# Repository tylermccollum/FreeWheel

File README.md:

BLDC motors represent an opportunity for massive improvements in hobby 
robotics work, but is largely limited by the cost. You can get a 
serviceable motor for less than $5, but the driver to use it starts at 
$40. The goal for this project is to create an open-source 100W BLDC 
servo controller design with a BOM cost under $10 and an accompanying 
library for control to standardize open-source FOC work.

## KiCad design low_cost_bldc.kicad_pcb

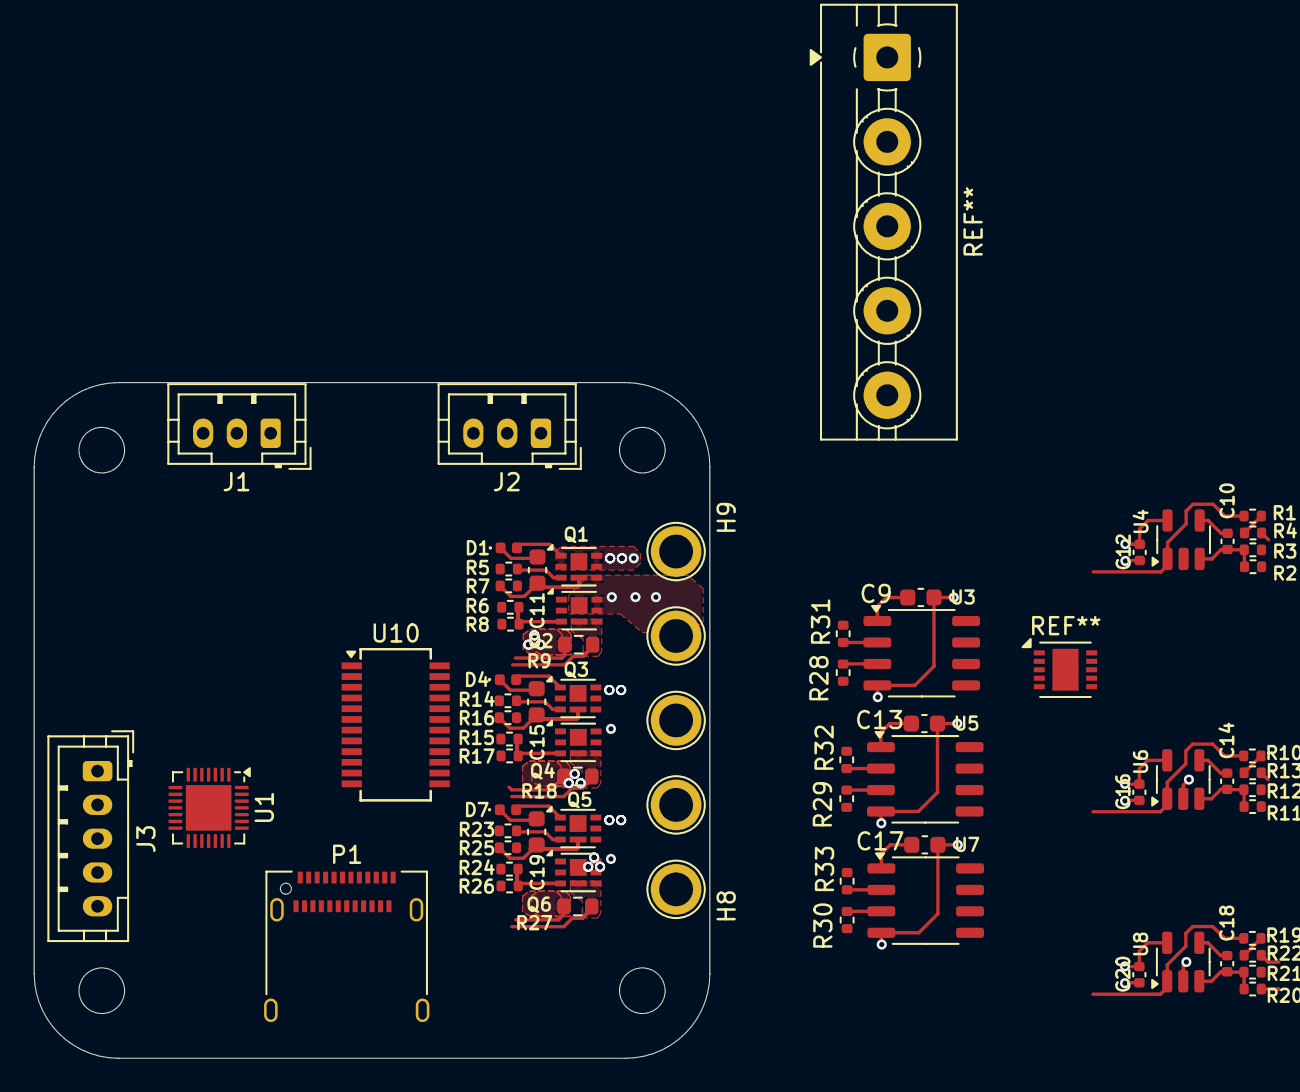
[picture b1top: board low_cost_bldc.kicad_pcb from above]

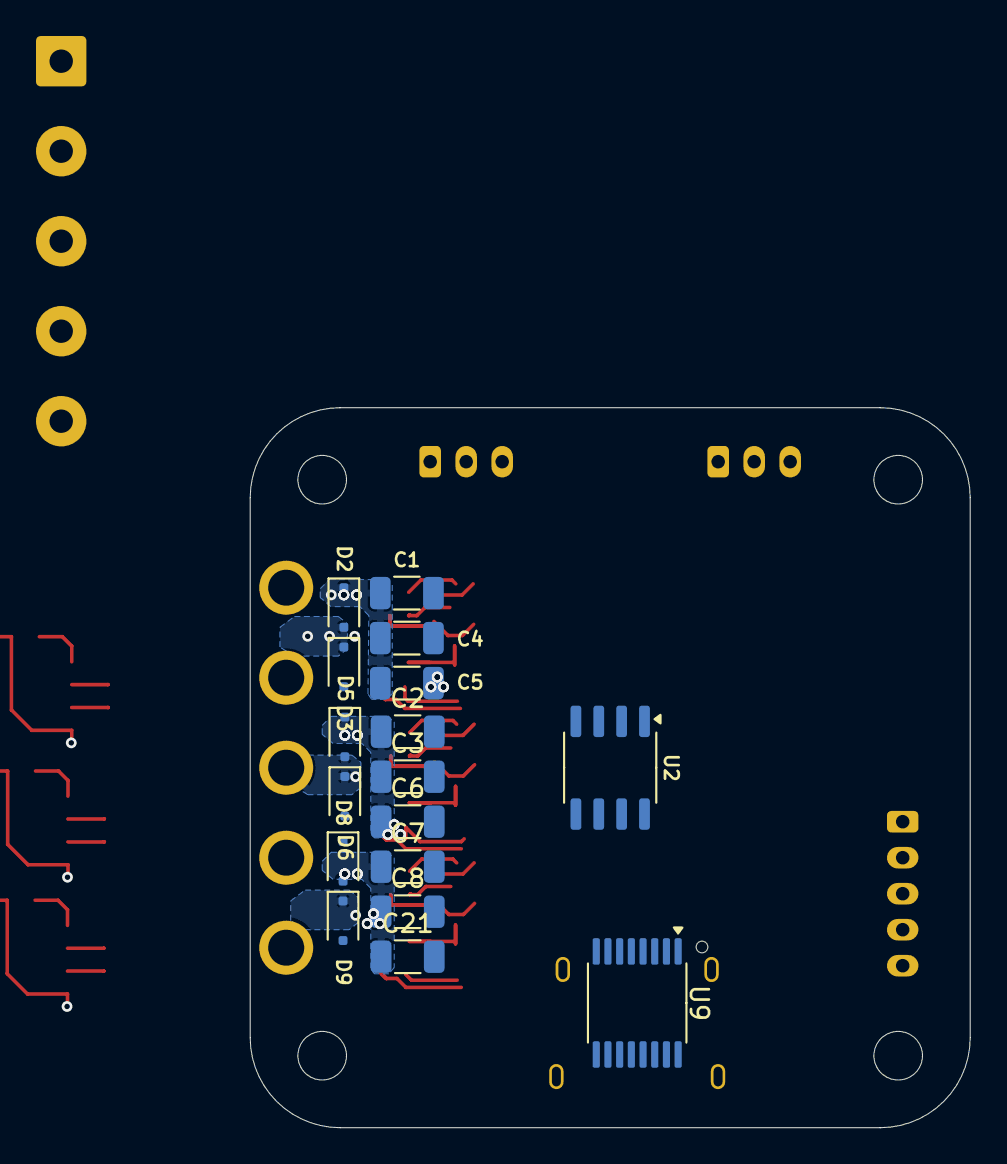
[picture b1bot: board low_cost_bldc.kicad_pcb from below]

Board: 4 copper layers, 40.0 x 40.0 mm, 92 parts (17 on the bottom side), 43 nets.

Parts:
C1, C2, C3, C4, C5, C6, C7, C8, C21: 10uF; C_1206_3216Metric
C9, C11, C13, C15, C17, C19: 1uF; C_0603_1608Metric
C10, C14, C18: C_Small; C_0402_1005Metric
C12, C16, C20: 0.1uF; C_0402_1005Metric
D1, D4, D7: D_Schottky_Filled; D_0402_1005Metric
D2, D3, D5, D6, D8, D9: D_Schottky_Filled; D_SOD-323F
H1, H2, H3, H4: MountingHole; MountingHole_2.7mm_M2.5
H5, H6, H7, H8, H9: MountingHole_Pad; TestPoint_Plated_Hole_D2.0mm
J1, J2: Conn_01x03; JST_PH_B3B-PH-K_1x03_P2.00mm_Vertical
J3: Conn_01x05; JST_PH_B5B-PH-K_1x05_P2.00mm_Vertical
P1: USB_C_Plug_USB2.0; USB_C_Receptacle_Amphenol_12401610E4-2A
Q1, Q2, Q3, Q4, Q5, Q6: HSCB3014; DFN-6-1EP_2x2mm_P0.65mm_2xEP
R1, R2, R10, R11, R19, R20: 47k; R_0402_1005Metric
R3, R4, R12, R13, R21, R22, R28, R29, R30, R31, R32, R33: 10k; R_0402_1005Metric
R5, R6, R14, R15, R23, R24: 10; R_0402_1005Metric
R7, R8, R16, R17, R25, R26: 1k; R_0402_1005Metric
R9, R18, R27: 10m; R_0603_1608Metric
U1: CH32V203GxUx; QFN-28-1EP_4x4mm_P0.4mm_EP2.7x2.7mm
U2: MT6701CT; SO-8_3.9x4.9mm_P1.27mm
U3, U5, U7: U2115C; SOP-8_3.9x4.9mm_P1.27mm
U4, U6, U8: COS8051; SOT-23-5
U9: IP2721; TSSOP-16_4.4x5mm_P0.65mm
U10: UC6310; SSOP-24_3.9x8.7mm_P0.635mm

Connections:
+3V3: C12.1, C16.1, C20.1, R28.2, R29.2, R30.2, U4.5 (VS+), U6.5 (VS+), U8.5 (VS+)
+12V: C9.1, C13.1, C17.1, U3.1 (VCC), U5.1 (VCC), U7.1 (VCC)
/Half-Bridge U/I_SENSE: R1.1, U4.1
/Half-Bridge U/PWM_HI: R31.2, U3.2 (HIN)
/Half-Bridge U/~PWM_LO: R28.1, U3.3 (~LIN)
/Half-Bridge V/I_SENSE: R10.1, U6.1
/Half-Bridge V/PWM_HI: R32.2, U5.2 (HIN)
/Half-Bridge V/~PWM_LO: R29.1, U5.3 (~LIN)
/Half-Bridge W/I_SENSE: R19.1, U8.1
/Half-Bridge W/PWM_HI: R33.2, U7.2 (HIN)
/Half-Bridge W/~PWM_LO: R30.1, U7.3 (~LIN)
/PHASE_U: C11.2, D2.2 (A), D3.1 (K), H5.1, Q1.4 (S), Q1.8 (S), Q2.1 (D), Q2.2 (D), Q2.5 (D), Q2.6 (D), Q2.7 (D), R7.2, U3.6 (VS)
/PHASE_V: C15.2, D5.2 (A), D6.1 (K), H6.1, Q3.4 (S), Q3.8 (S), Q4.1 (D), Q4.2 (D), Q4.5 (D), Q4.6 (D), Q4.7 (D), R16.2, U5.6 (VS)
/PHASE_W: C19.2, D8.2 (A), D9.1 (K), H7.1, Q5.4 (S), Q5.8 (S), Q6.1 (D), Q6.2 (D), Q6.5 (D), Q6.6 (D), Q6.7 (D), R25.2, U7.6 (VS)
GND: C1.2, C2.2, C3.2, C4.2, C5.2, C6.2, C7.2, C8.2, C9.2, C12.2, C13.2, C16.2, C17.2, C20.2, C21.2, D3.2 (A), D6.2 (A), D9.2 (A), H8.1, R2.1, R4.2, R8.2, R9.2, R11.1, R13.2, R17.2, R18.2, R20.1, R22.2, R26.2, R27.2, R31.1, R32.1, R33.1, U3.4 (COM), U4.2 (VS-), U5.4 (COM), U6.2 (VS-), U7.4 (COM), U8.2 (VS-)
unnamed: C11.1, D1.1 (K), U3.8 (VB)
unnamed: C15.1, D4.1 (K), U5.8 (VB)
unnamed: C19.1, D7.1 (K), U7.8 (VB)
unnamed: P1.A1 (GND), P1.A12 (GND), P1.B1 (GND), P1.B12 (GND)
unnamed: P1.A4 (VBUS), P1.A9 (VBUS), P1.B4 (VBUS), P1.B9 (VBUS)
unnamed: Q1.3 (G), R5.2, R7.1
unnamed: Q2.3 (G), R6.2, R8.1
unnamed: Q2.4 (S), Q2.8 (S), R3.2, R9.1
unnamed: Q3.3 (G), R14.2, R16.1
unnamed: Q4.3 (G), R15.2, R17.1
unnamed: Q4.4 (S), Q4.8 (S), R12.2, R18.1
unnamed: Q5.3 (G), R23.2, R25.1
unnamed: Q6.3 (G), R24.2, R26.1
unnamed: Q6.4 (S), Q6.8 (S), R21.2, R27.1
unnamed: U1.16 (VSS), U1.29 (VSS)
unnamed: R5.1, U3.7 (HO)
unnamed: R6.1, U3.5 (LO)
unnamed: C10.1, R2.2, R3.1, U4.3 (+)
unnamed: C10.2, R1.2, R4.1, U4.4 (-)
unnamed: R14.1, U5.7 (HO)
unnamed: R15.1, U5.5 (LO)
unnamed: C14.1, R11.2, R12.1, U6.3 (+)
unnamed: C14.2, R10.2, R13.1, U6.4 (-)
unnamed: R23.1, U7.7 (HO)
unnamed: R24.1, U7.5 (LO)
unnamed: C18.1, R20.2, R21.1, U8.3 (+)
unnamed: C18.2, R19.2, R22.1, U8.4 (-)
VBUS: C1.1, C2.1, C3.1, C4.1, C5.1, C6.1, C7.1, C8.1, C21.1, D1.2 (A), D2.1 (K), D4.2 (A), D5.1 (K), D7.2 (A), D8.1 (K), H9.1, Q1.1 (D), Q1.2 (D), Q1.5 (D), Q1.6 (D), Q1.7 (D), Q3.1 (D), Q3.2 (D), Q3.5 (D), Q3.6 (D), Q3.7 (D), Q5.1 (D), Q5.2 (D), Q5.5 (D), Q5.6 (D), Q5.7 (D)

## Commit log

2025-01-12 Add gitignore
2025-01-21 Top-only inverter layout
2025-01-21 Rough sketch-up of idea. Does introduce the problem of cooling the FETs now...
2025-01-21 Initial mounting holes, power lugs. Sitting at @ qty 10 BOM estimate. Still need 12V, 3.3V power; comms connectors
2025-01-21 Stop tracking backups
2025-01-22 Readme
2025-01-24 Readme, rough connector placement, inverter refinement, increase MCU pin count to have a chance of succeeding.
2025-02-15 Organizing
2025-02-15 Move connectors
2025-02-15 Re-save pcbdoc
